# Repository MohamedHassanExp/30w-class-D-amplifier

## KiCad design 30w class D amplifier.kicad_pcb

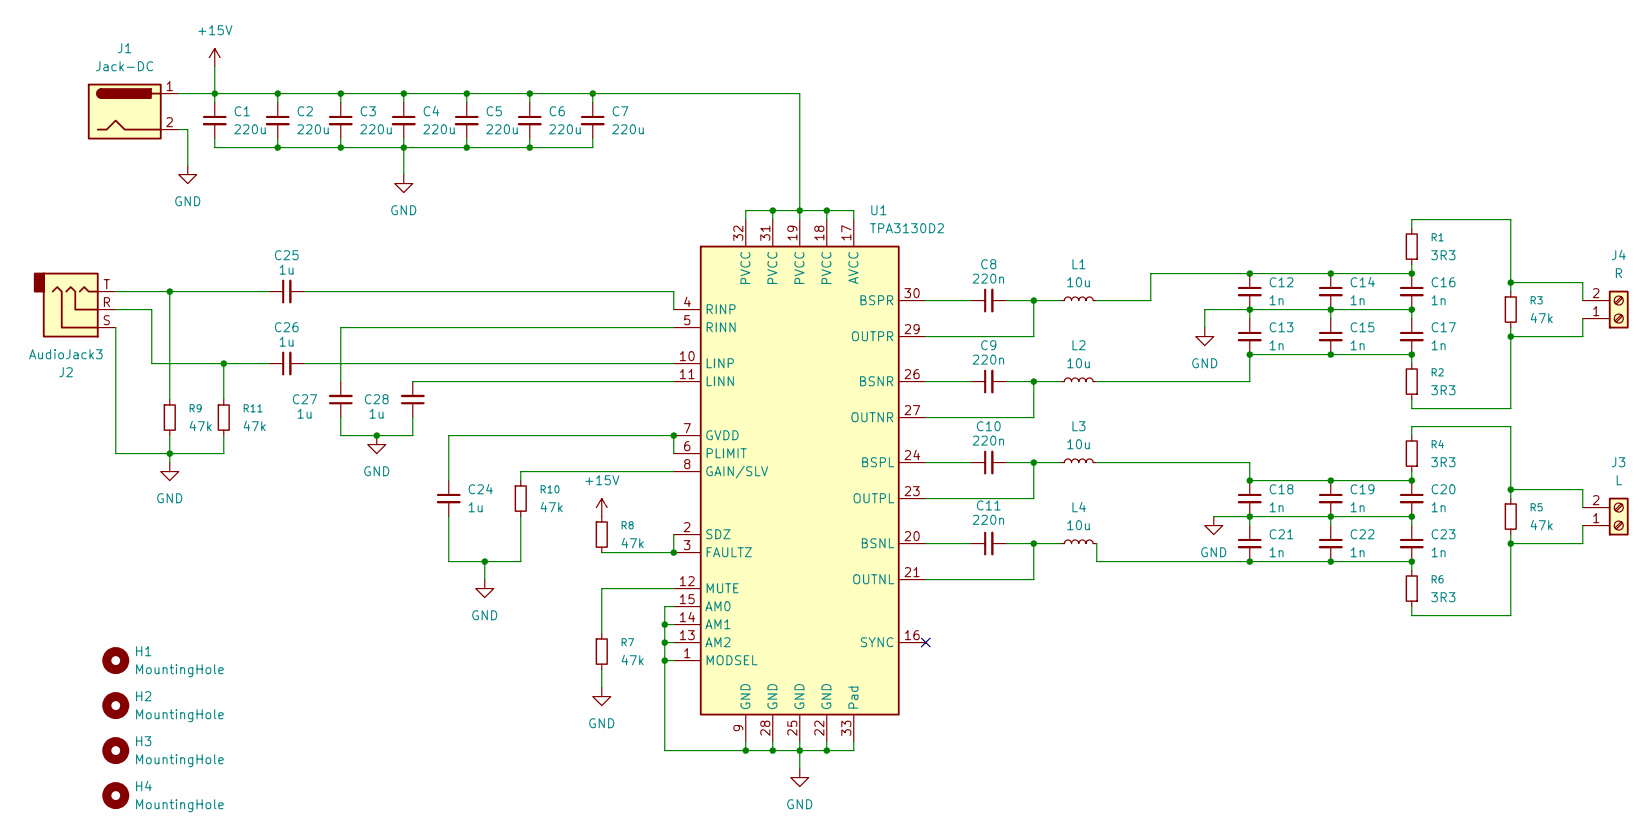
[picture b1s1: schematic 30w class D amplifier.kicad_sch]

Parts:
C1, C2, C3, C4, C5, C6, C7: 220u; C_0603_1608Metric
C8, C9, C10, C11: 220n; C_1206_3216Metric
C12, C13, C14, C15, C16, C17, C18, C19, C20, C21, C22, C23: 1n; C_0603_1608Metric
C24, C25, C26, C27, C28: 1u; C_0603_1608Metric
H1, H2, H3, H4: MountingHole; MountingHole_2.2mm_M2
J1: Jack-DC; BarrelJack_Horizontal
J2: AudioJack3; Jack_3.5mm_CUI_SJ1-3533NG_Horizontal
J3: L; TerminalBlock_Phoenix_MKDS-1,5-2-5.08_1x02_P5.08mm_Horizont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
J4: R; TerminalBlock_Phoenix_MKDS-1,5-2-5.08_1x02_P5.08mm_Horizont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
L1, L2, L3, L4: 10u; L_Bourns_SRN6045TA
R1, R2, R4, R6: 3R3; R_0603_1608Metric
R3, R5, R7, R8, R9, R10, R11: 47k; R_0603_1608Metric
U1: TPA3130D2; HTSSOP-32-1EP_6.1x11mm_P0.65mm_EP5.2x11mm_Mask4.11x4.36mm_T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

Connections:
+15V: C1.1, C2.1, C3.1, C4.1, C5.1, C6.1, C7.1, J1.1, R8.1, U1.17 (AVCC), U1.18 (PVCC), U1.19 (PVCC), U1.31 (PVCC), U1.32 (PVCC)
GND: C1.2, C2.2, C3.2, C4.2, C5.2, C6.2, C7.2, C12.2, C13.1, C14.2, C15.1, C16.2, C17.1, C18.2, C19.2, C20.2, C21.1, C22.1, C23.1, C24.2, C27.1, C28.1, J1.2, J2.S, R7.2, R9.2, R10.2, R11.2, U1.1 (MODSEL), U1.9 (GND), U1.13 (AM2), U1.14 (AM1), U1.15 (AM0), U1.22 (GND), U1.25 (GND), U1.28 (GND), U1.33 (Pad)
unnamed: C12.1, C14.1, C16.1, L1.2, R1.1
unnamed: C13.2, C15.2, C17.2, L2.2, R2.2
unnamed: C18.1, C19.1, C20.1, L3.2, R4.1
unnamed: C21.2, C22.2, C23.2, L4.2, R6.2
unnamed: C25.1, J2.T, R9.1
unnamed: C26.1, J2.R, R11.1
unnamed: J3.1, R5.2, R6.1
unnamed: J3.2, R4.2, R5.1
unnamed: J4.1, R2.1, R3.2
unnamed: J4.2, R1.2, R3.1
unnamed: C11.1, U1.20 (BSNL)
unnamed: C9.1, U1.26 (BSNR)
unnamed: C10.1, U1.24 (BSPL)
unnamed: C8.1, U1.30 (BSPR)
unnamed: R8.2, U1.2 (SDZ), U1.3 (FAULTZ)
unnamed: R10.1, U1.8 (GAIN/SLV)
unnamed: C24.1, U1.6 (PLIMIT), U1.7 (GVDD)
unnamed: C28.2, U1.11 (LINN)
unnamed: C26.2, U1.10 (LINP)
unnamed: R7.1, U1.12 (MUTE)
unnamed: C11.2, L4.1, U1.21 (OUTNL)
unnamed: C9.2, L2.1, U1.27 (OUTNR)
unnamed: C10.2, L3.1, U1.23 (OUTPL)
unnamed: C8.2, L1.1, U1.29 (OUTPR)
unnamed: C27.2, U1.5 (RINN)
unnamed: C25.2, U1.4 (RINP)

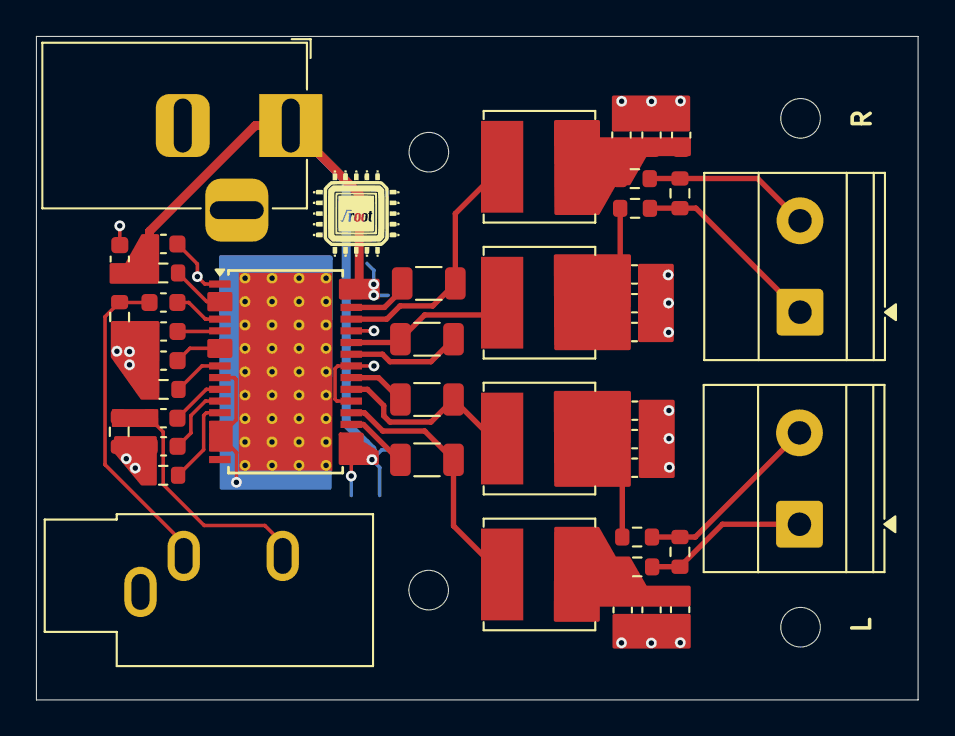
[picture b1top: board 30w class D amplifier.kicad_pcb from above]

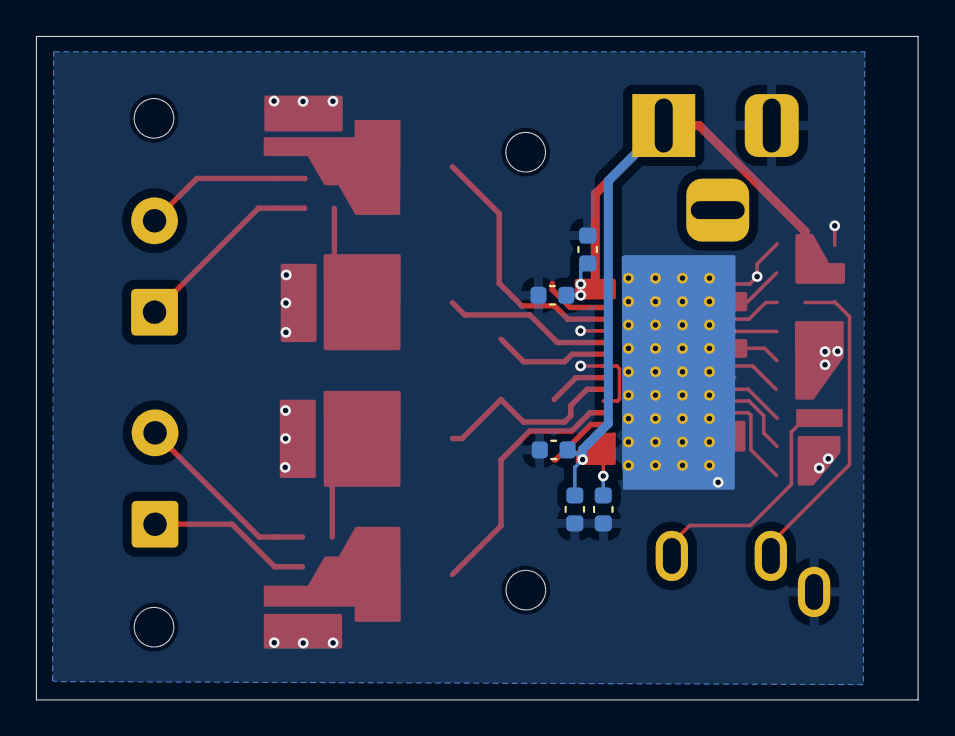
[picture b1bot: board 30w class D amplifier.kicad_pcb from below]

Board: 2 copper layers, 49.0 x 36.9 mm, 52 parts (5 on the bottom side), 28 nets.

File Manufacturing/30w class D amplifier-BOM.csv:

"Id";"Designator";"Footprint";"Quantity";"Designation";"Supplier and ref";
1;"C24,C27,C25,C26,C28";"C_0603_1608Metric";5;"1u";;;
2;"R11,R5,R3,R8,R9,R7,R10";"R_0603_1608Metric";7;"47k";;;
3;"C12,C18,C19,C22,C13,C20,C16,C15,C14,C21,C17,C23";"C_0603_1608Metric";12;"1n";;;
4;"J1";"BarrelJack_Horizontal";1;"Jack-DC";;;
5;"C10,C11,C9,C8";"C_1206_3216Metric";4;"220n";;;
6;"L4,L2,L1,L3";"L_Bourns_SRN6045TA";4;"10u";;;
7;"J3";"TerminalBlock_Phoenix_MKDS-1,5-2-5.08_1x02_P5.08mm_Horizontal";1;"L";;;
8;"U1";"HTSSOP-32-1EP_6.1x11mm_P0.65mm_EP5.2x11mm_Mask4.11x4.36mm_ThermalVias";1;"TPA3130D2";;;
9;"R6,R2,R4,R1";"R_0603_1608Metric";4;"3R3";;;
10;"J4";"TerminalBlock_Phoenix_MKDS-1,5-2-5.08_1x02_P5.08mm_Horizontal";1;"R";;;
11;"C7,C6,C1,C4,C2,C5,C3";"C_0603_1608Metric";7;"220u";;;
12;"J2";"Jack_3.5mm_CUI_SJ1-3533NG_Horizontal";1;"AudioJack3";;;
